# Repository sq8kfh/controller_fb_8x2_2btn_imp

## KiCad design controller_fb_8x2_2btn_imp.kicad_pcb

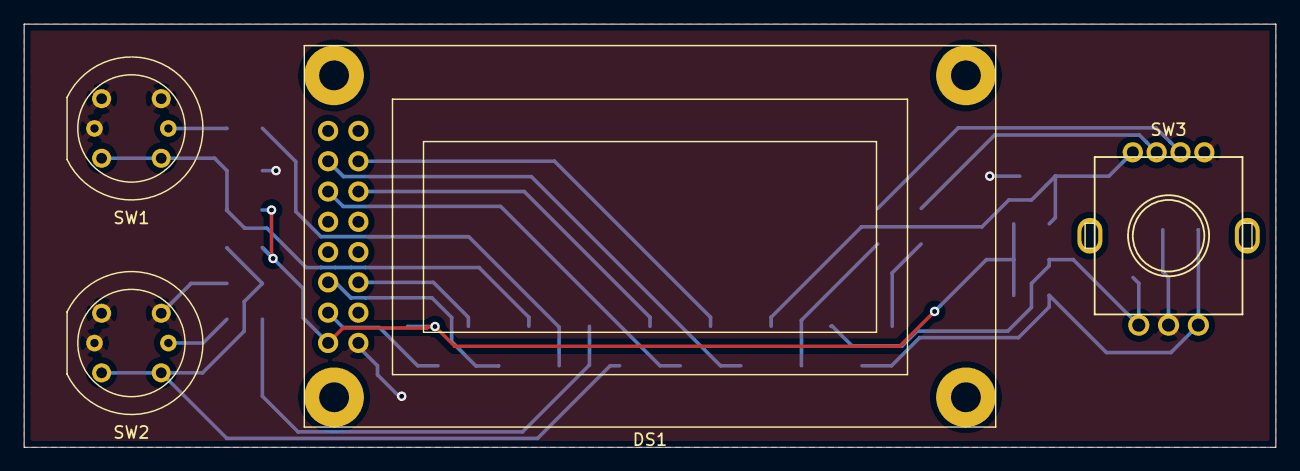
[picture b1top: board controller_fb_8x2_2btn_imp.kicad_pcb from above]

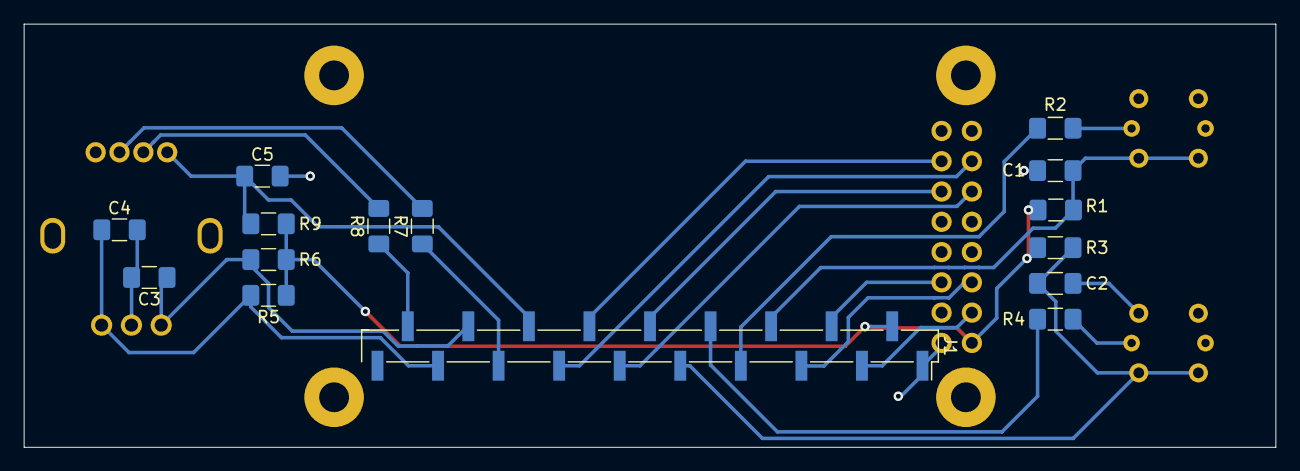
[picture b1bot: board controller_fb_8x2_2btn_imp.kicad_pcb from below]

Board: 2 copper layers, 105.0 x 35.5 mm, 19 parts (15 on the bottom side), 22 nets.

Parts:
C1, C2, C3, C4, C5: 100nF; C_1206_3216Metric_Pad1.42x1.75mm_HandSolder
DS1: RS0010; REC000802A
J1: Conn_01x19; PinHeader_1x19_P2.54mm_Vertical_SMD_Pin1Right
R1, R3, R5, R6, R9: 10k; R_1206_3216Metric_Pad1.42x1.75mm_HandSolder
R2, R4, R7, R8: 470R; R_1206_3216Metric_Pad1.42x1.75mm_HandSolder
SW1, SW2: SW_Push_LED; SW_PUSH_HIGHLY_KS01-BL
SW3: Rotary_Encoder_with_Dual_LED_and_Switch; PEL12D-4xxxS-Sxxxx

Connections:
+5V: DS1.2, J1.2, R1.1, R3.1, R5.1, R6.1, R9.1
/PB0(MISO): DS1.4, J1.3
/PB1(MOSI): DS1.5, J1.4
/PB2(INT1): C2.2, J1.9, R3.2, SW2.2
/PB3: C5.1, J1.14, R9.2, SW3.4
/PB4: J1.15, R7.1
/PB5(INT2): C3.1, J1.16, R6.2, SW3.A
/PB6: C4.1, J1.17, R5.2, SW3.B
/PB7(SCK): DS1.6, J1.5
/PC4: DS1.11, J1.10
/PC5: DS1.12, J1.11
/PC6: DS1.13, J1.12
/PC7(D2A): DS1.14, J1.13
/PD0: J1.18, R8.1
/PD5: C1.2, J1.6, R1.2, SW1.2
/PD6: J1.7, R2.2
/PD7: J1.8, R4.2
GND: C1.1, C2.1, C3.2, C4.2, C5.2, DS1.1, J1.1, SW1.1, SW1.3, SW2.1, SW2.3, SW3.1, SW3.C
unnamed: R2.1, SW1.4
unnamed: R4.1, SW2.4
unnamed: R7.2, SW3.2
unnamed: R8.2, SW3.3

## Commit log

2020-12-22 Init v0.1
2020-12-22 Init v0.2
    - Unifying a button connections
    - Enlarge button holes
    - Decrease PCB high -0.2mm x 2
